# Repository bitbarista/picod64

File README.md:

# PicoD64: a cycle-exact 1541 emulator you can build

<div align="center">

-0369a1)

</div>

PicoD64 replaces a Commodore 1541 disk drive, using a Raspberry Pi Pico 2. It doesn't imitate
the drive's behaviour from the outside: it **emulates the 1541's electronics**. The drive's 6502,
its two 6522 VIAs and the GCR data path to the head are emulated cycle by cycle, in lockstep at
1 MHz, and they run the 1541's own DOS ROM, which you supply. Disk images come from a microSD
card, and it plugs into the C64's serial (IEC) port like a drive. Because the DOS and any drive
code a program uploads run cycle for cycle, fast loaders behave as they do on a 1541: demanding demo loaders
run on a real C64 (see [Compatibility](#compatibility)).

It is designed to be cheap and easy to build: a small board, almost all through-hole (the
microSD socket and the Pico 2's castellated edge are surface-soldered), a Pico 2, a 1.3" OLED,
a rotary encoder and a 3D-printed case.

> **Free for private and commercial use.** PicoD64 is a hobby project, given to the community.
> Build one, sell them, improve them; if you change it, share your changes under the same terms
> (see [Licence](#licence)). If it's useful to you, please consider
> [supporting it on Ko-fi](https://ko-fi.com/bitbarista). It funds the prototypes and test hardware.
>
> **Ordering boards?** Signing up to JLCPCB through [this referral link](https://jlcpcb.com/?from=PBTJYEXOJNFQR) costs you nothing
> extra and earns the project a small credit towards new prototypes.

<div align="center">
  
</div>

## Download

Click a link and the file downloads; there's no need to find your way round GitHub.

| | |
|---|---|
| **Firmware** | [**picod64.uf2**](https://github.com/bitbarista/picod64/releases/latest/download/picod64.uf2): copy it onto the Pico (see [Firmware and SD card](#firmware-and-sd-card)). |
| **The 1541 ROM for the SD card** | The [**card setup page**](https://bitbarista.github.io/picod64/fw/tools/card-setup.html) fetches it, checks it and saves it for the card. |
| **The board** | [**picod64-rev1.1-gerbers.zip**](https://github.com/bitbarista/picod64/releases/latest/download/picod64-rev1.1-gerbers.zip): send this file to a PCB maker as it is. |
| **The case** | [**picod64-case-stl.zip**](https://github.com/bitbarista/picod64/releases/latest/download/picod64-case-stl.zip): every part to print, as STL files. |
| **Using it** | The [**user guide**](docs/USER-GUIDE.md): the browser, the knob and OLED, and multi-disk games, with pictures. |
| **Building it** | The [**interactive BOM**](https://bitbarista.github.io/picod64/hardware/fab/picod64-ibom.html) shows where each part goes; [`hardware/BUILD-NOTES.md`](hardware/BUILD-NOTES.md) is the step-by-step guide. |
| **Everything** | [**The whole project as one zip**](https://github.com/bitbarista/picod64/archive/refs/heads/main.zip): the source, the parts lists and all the documents. |

Older versions and the notes for each are on the [Releases page](https://github.com/bitbarista/picod64/releases).

## Highlights

| | |
|---|---|
| **Change disks with one hold of the knob.** For multi-disk games and demos: hold the knob and PicoD64 swaps to the next disk of the set, as you'd swap floppies, and the C64 carries on. The OLED shows which disk is in (`2/3`). | **A knob and display on the drive.** Insert, swap and eject disks, make a new blank one, or set the device number, without touching the C64. Everything the browser does is shown there too. See the [user guide](docs/USER-GUIDE.md). |
| **The 1541's electronics, emulated.** The drive's 6502, VIAs and GCR path are emulated cycle by cycle, running the 1541's own DOS ROM. Fast loaders and drive code should behave as they do on a 1541. | **Cheap and easy to build.** A Raspberry Pi Pico 2 and common parts, almost all through-hole, with ready-made Farnell and LCSC order files. No programmer: flash it by copying one file over USB. |
| **An all-new browser, built in.** Nothing to install on the card or the C64: `LOAD"*",8`, `RUN`. Full upper/lower-case names, a format column, multi-disk sets told apart, type to filter, keyboard or joystick. | **Turbo loading, ~27× faster.** About 11 KB/s with no drive code, and it falls back to a plain load on any error. One key turns it off for awkward or copy-protected titles. |
| **A case designed for it.** A 3D-printed case made to fit this board, with C64-style ribs, shoulders and printed badges, including a PWR/ACT badge like the breadbin's POWER badge. Prints without supports or a brim, and every part is fit-checked against it. | **Writes for real.** SAVE, scratch and format go back into the D64 on the card. With no disk mounted, `SAVE` writes a PRG and `N:` makes a new blank disk. |
| **Sounds like a 1541.** A piezo plays the head stepping, the head bump knock and the motor, driven by what the emulated drive is doing. | **Fits in with what you have.** A second IEC socket daisy-chains on to other drives, device 8–11. Made for FB64 and FB64 Turbo, and for JiffyDOS with your own ROM (both pass the PC tests; not yet confirmed on a real C64). |

**Open.** Hardware CERN-OHL-W, code GPL-3.0. Written clean-room from datasheets and Commodore's own documents, with every source listed.

**Proven on a real C64:** the drive and its DOS, the browser and its turbo, and a list of demanding demo loaders and the 1541 Testsuite (see [Compatibility](#compatibility)). JiffyDOS (KERNAL, and KERNAL plus drive ROM) is proven on a real C64 too. FB64 and the turbo's speed figure come from the PC tests so far: [Status](#status-rev-11-november-2026) says what is proven where.

## What it does

In detail.

- **The 1541, emulated cycle for cycle.** Every cycle of the drive's 6502 and VIAs is emulated, in
  lockstep with the IEC bus, running the stock DOS ROM (325302-01 + 901229-05) that you supply on the card.
  SAVE, scratch and format work, and what you write goes back into the D64 on the card. With no disk
  mounted, `SAVE` writes a PRG to the card, and `N:NAME,ID` makes a new blank D64. The knob's **Settings** has **New disk** too.
- **D64 images from microSD**, up to 42 tracks. FAT32 or exFAT, any size, folders anywhere. A mounted image is
  streamed to GCR a track at a time. Written tracks go back to the file when the motor stops,
  before a disk swap or an eject, and when the card-detect switch sees the card being pulled
  (eject first to be safe).
- **Browse mode.** With no disk mounted, the C64 sees the card itself: `LOAD"$",8` lists the
  folder, `.PRG` files load directly, and you `CD` into a folder or a D64 to mount it.
- **A built-in browser for the C64.** `LOAD"*",8` then `RUN`, or `LOAD"BROWSER",8` the plain way. Full
  names in upper and lower case, with a column showing each file's format, so `game.d64`, `game.prg` and
  `game.crt` can be told apart, and a footer that says what RETURN will do. Keyboard or joystick in port 2:
  cursor keys and RETURN, type to filter, DEL for back, F1 for options (Run, Load, Run slow; for a disk Open,
  Run first, Insert), RUN/STOP to quit. Folders of any size; up to 2,048 entries are listed, and the filter
  reaches the rest. It remembers the turbo setting, the folder and the position on the card.
- **A turbo for the browser.** Programs (PRG files) on the card load at about 11 KB/s, ~27× stock (on
  the PC twin), with no drive code. Programs inside a D64 load the normal 1541 way, through the drive, so the
  drive has read the disk as a real one would. F3 turns it off, F1 Run slow skips it once, and any wrong byte falls
  back to a plain LOAD.
- **FB64 file browsers.** Made to work with Jani's **FB64** (FB v2.0), its fast-loader version
  **FB v2.0FL**, and **FB64 Turbo** ([CSDb 223021](https://csdb.dk/release/?id=223021)): browsing,
  mounting and loading, including FB64 Turbo's turbo loads from a D64 or a PRG. All three pass on
  the PC against the real KERNAL; the first board will try them on a real C64.
- **Display and knob.** A 1.3" OLED shows the folder and the mounted disk. The knob scrolls, pushes
  to mount and ejects. **Settings** is the last line of the list, one click back from the top. A **long press mounts the next disk of a set** (`disk1`, `side a`,
  `1a`, `(Disk 1 of 3)` and similar names), for multi-disk games and demos. A green PWR and a red ACT
  LED, the 1541's colours, stand proud of the lid.
  **Try it before you build:** [open the front panel demo](https://bitbarista.github.io/picod64/host/panel-demo/panel-demo.html)
  in your browser. It runs the real knob and OLED code, in a picture of the case. To keep a copy that works offline,
  download [`panel-demo.html`](host/panel-demo/panel-demo.html) and open it.
- **Daisy chain.** Two IEC sockets wired in parallel: one to the C64, one on to the next device.
  The device number can be set to 8–11: hold the knob at power-on, turn, press. It is shown on the OLED.
- **It sounds like a 1541.** A small piezo plays the head stepping, the knock of a head
  bump and the motor, driven by what the emulated drive is really doing. *Sound* in the knob's **Settings** turns it off.
- **Powered by USB.** An optional header takes 5 V from the C64's datasette port instead, but
  that port is rated for only about 100 mA, so whether it is enough is still to be measured.

## The built-in browser

There's nothing to install or copy to the card, and nothing to add to the C64. It's in the firmware: `LOAD"*",8`, then `RUN`.

- **Fast.** Programs load at about 11 KB/s, roughly 27 times stock, with no drive code. It's measured on the PC test setup so far, not yet on a real C64.
- **You can see what you're choosing.** Full names in upper and lower case. A format column tells `game.d64` from `game.prg` and `game.crt`, and a footer says what RETURN will do.
- **Which disk is which.** A column reads the disk and side from the name, so a long name's `(Disk 1 of 2 Side A)` shows as `1A` even when the row has to shorten it.
- **Made for real collections.** A folder of 802 long names opens in about 0.75 s on the test setup, with up to 2,048 entries listed in order. Type a few letters to filter, including entries past that limit.
- **Keyboard or joystick.** Cursor keys and RETURN, DEL for back, F1 for options (Run, Load, Run slow; on a disk Open, Run first, Insert), F3 for the turbo. It's all on screen, so there's nothing to memorise.
- **Remembers where you were.** The folder, your position and the turbo setting are kept on the card.
- **Fits in with what you have.** It's designed to start with a fast-load cartridge fitted, runs with a JiffyDOS KERNAL on the test setup, and works on a plain 1541 too. FB64 and others still work if you prefer them: none of this needs the browser.

## Status (rev 1.1, November 2026)

- **The first board is built and works with a real C64.** Rev 1.1 is the same board with the new name on the
  silkscreen; copper and drill files are identical ([`hardware/AUDIT.md`](hardware/AUDIT.md) R25).
- **The emulator is proven on the PC.** The 6502 passes Klaus Dormann's functional test and is
  bus-identical, cycle by cycle, to perfect6502. The stock DOS boots exactly as in VICE. The
  real C64 KERNAL lists and loads from it over a simulated IEC bus, byte-identical to VICE.
  Writes are read back correctly by VICE's `c1541`.
- **The board firmware is built and host-tested.** The drive runs in real time on a Pico 2
  (lockstep at 150 MHz). The whole board code (SD, FatFs, browse mode, mount, write-back,
  fast-loader handling, knob, OLED) is tested on the PC against the real KERNAL and a simulated
  SD card ([`host/fwtwin.sh`](host/fwtwin.sh), over 100 checks).
- **On a real C64, at the stock 150 MHz:** the DOS, the browser and its fast loader, and demanding demo loaders
  (The Hat, Edge of Disgrace, MATH, each through every disk), checked against a real-timing drive on the same C64
  with a bus sniffer. [`FIRMWARE.md`](FIRMWARE.md) has the measurements and the known issues.
- **The case is printed:** the split lid, C64-style details, badges and knob are confirmed by print. A fit check of
  every part on the assembled board against the case passes ([`case/check_fit.py`](case/check_fit.py)).

**Still to measure:** power from the datasette port; more fast loaders and games.

**Known limits.** D64 images of 35, 40 and 42 tracks. A D64's error bytes are built into the disk, so the DOS
finds each read error where the original disk had it; the write errors they can record are not. No G64, no D71/D81. The 6502's undocumented opcodes pass the 1541 Testsuite; its IRQ/SO edge
timing is not yet checked against perfect6502.

## Compatibility

Tested on a real **PAL** C64 with the stock 150 MHz firmware, PicoD64 the only device on the serial bus, each
title from a freshly powered-up C64 and run to its end (or its own pass screen):

- **Demos and their loaders:** Coma Light 13 (Krill's loader), Dutch Breeze, Edge of Disgrace and Uncensored
  (Booze Design), Lunatico and Shards of Fancy (Spindle), MATH, Memento Mori (Sparkle), Primitive 7 Sins,
  Reanim8ed (Dasheles' loader), The Hat, The Masque, Transwarp (the fastest loader about), Wonderland XIV (40
  tracks), Mafio-DOS.
- **The drive's CPU:** the 1541 Testsuite (r192), all 219 tests.
- **The browser and its turbo,** loading PRGs (turbo) and D64s (the normal 1541 way) from the card.

That is a sample, not every program. PicoD64 is checked against a real 1541 wherever we could, but **we can't
be sure everything runs**: some loaders are famously picky, and there are thousands of titles.
[`docs/COMPAT-TESTS.md`](docs/COMPAT-TESTS.md) has the list, with each title's loader and disks. Some fast loaders fail with another drive
or interface on the serial bus, on a real 1541 too: if one fails, try PicoD64 as the only device.

**PAL only so far.** Every test was on a PAL C64. PicoD64 is designed for NTSC too (the drive runs on its own 1 MHz
clock, as a 1541 does, and the browser's turbo allows for both C64 clocks), but it has **not been tested on an NTSC
C64**. Reports from NTSC owners are welcome (the bug report link below).

**If something doesn't work, please [open an issue](https://github.com/bitbarista/picod64/issues/new?template=bug_report.md).**
Say what you ran (title, group, and a CSDb link or where the image came from), how you started it (the browser,
`LOAD"*",8,1`, a cartridge), what happened and when, and which firmware ([`firmware/VERSION.txt`](firmware/VERSION.txt)). If you have a
real 1541 or another drive to hand, whether it works there helps a lot.

## How it works

- **Two cores.** Core 1 owns the IEC pins and nothing else. It runs either browse mode or the
  emulated 1541, from SRAM, in lockstep with the bus. Core 0 owns the SD card, the OLED, the
  knob, the LEDs and the piezo. When browse mode needs the card, core 1 holds the bus busy, as a
  real drive does, while core 0 does the work.
- **The ATN acknowledge in PIO.** A real 1541 answers ATN with an XOR gate, in nanoseconds. Some
  fast loaders, FB64 Turbo among them, check for the answer 4 µs later, too soon for software,
  so a PIO state machine ([`fw/atn_gate.pio`](fw/atn_gate.pio), 5 instructions) answers instead. Measured on the
  bus of a real C64: DATA follows an ATN edge 0.17 µs later when pulled, 0.42 µs when released (the
  line's slower rise); a 1541 on the same C64, 0.25 µs.
- **Fast loaders from browse mode.** When a C64 program uploads drive code in browse mode,
  PicoD64 builds a disk on the card, boots the emulated 1541 with its DOS, replays the conversation
  into it, then hands the bus to the emulated drive.
- **White-coat design.** PicoD64's own code is written from primary documentation: datasheets,
  Commodore's documents and the ROM itself. Other implementations, VICE among them, are used
  only as black-box oracles to compare results against. [`PROVENANCE.md`](PROVENANCE.md) lists every source and
  the few exceptions (FB64 Turbo's source was read, for compatibility only). Third-party code,
  FatFs, keeps its own licence ([`THIRD-PARTY.md`](THIRD-PARTY.md)).

## Building one

1. **Order the board** from JLCPCB ([referral link](https://jlcpcb.com/?from=PBTJYEXOJNFQR)) or
   any fab: [`picod64-rev1.1-gerbers.zip`](https://github.com/bitbarista/picod64/releases/latest/download/picod64-rev1.1-gerbers.zip) (also in [`hardware/fab/`](hardware/fab/)), 2 layers, 1.6 mm.
2. **Buy the parts:** [`hardware/fab/BUY.md`](hardware/fab/BUY.md), with a ready-made Farnell upload file in [`hardware/fab/`](hardware/fab/). Farnell
   is the tested source; an LCSC file is there too, but it has never been ordered. The full BOM, with the optional parts, is [`hardware/fab/BOM.md`](hardware/fab/BOM.md).
3. **Solder it.** Almost everything is through-hole. The interactive BOM
   ([open it](https://bitbarista.github.io/picod64/hardware/fab/picod64-ibom.html), or download
   [`hardware/fab/picod64-ibom.html`](hardware/fab/picod64-ibom.html) and open it in a browser)
   shows where each part goes and lets you tick parts off as you fit them. The Pico 2 is soldered flat by its
   castellated edge, and the microSD socket is surface-mount, with every tail reachable by an iron.
   **[`hardware/BUILD-NOTES.md`](hardware/BUILD-NOTES.md) is the step-by-step build:** fit order, polarities, LED standoffs, the OLED,
   the first test, printing and assembling the case.
4. **Print the case:** every file in [`picod64-case-stl.zip`](https://github.com/bitbarista/picod64/releases/latest/download/picod64-case-stl.zip) (the same as [`case/stl/`](case/stl/)), as exported, with **no brim** and no supports
   ([`hardware/BUILD-NOTES.md`](hardware/BUILD-NOTES.md), step 6). The badges print best in two colours: change filament
   at the letters. The set includes a small **knob seating tool**: push the knob onto it once before fitting it, so its
   first, firm push is on the bench and not on the encoder ([`hardware/BUILD-NOTES.md`](hardware/BUILD-NOTES.md), step 7).
5. **Flash the firmware and prepare the card** (below).

### Firmware and SD card

- **Flash:** hold the Pico's BOOTSEL (in the case: press the pinhole marked ⤓ with a paperclip),
  plug in USB, and copy [**picod64.uf2**](https://github.com/bitbarista/picod64/releases/latest/download/picod64.uf2) (click to download; it's also [`firmware/picod64.uf2`](firmware/picod64.uf2)) onto
  the **RP2350** drive that appears.
- **Updating, once flashed:** copy the new `picod64.uf2` to the card's top folder and switch on. PicoD64
  checks it, installs it (the OLED says *Updating, wait*, then *Updated*) and renames it
  `picod64.uf2.done`. Don't switch off while it updates; if that ever happens, flash it with BOOTSEL as above.
- **SD card:** any size, formatted FAT32 or exFAT. Put your disk images (`.d64`) and programs
  (`.prg`) on it, in folders if you like.
- **The 1541 DOS ROM.** PicoD64's emulated 1541 runs the drive's own operating system, so it needs a
  copy of the drive's ROM. The ROM is Commodore's copyright, so PicoD64 can't include it; you put it on the
  card yourself. The ROMs are archived at [zimmers.net](https://www.zimmers.net/anonftp/pub/cbm/firmware/).
  - **The easy way, any computer:** open the **[card setup page](https://bitbarista.github.io/picod64/fw/tools/card-setup.html)**
    and click *Get the 1541 ROM*. It fetches the ROM from zimmers.net, joins and checks it, and saves `dos1541.bin`
    for the card (in Chrome or Edge, straight onto the card). It takes your own copy instead if you have one, and
    can add the Commodore font for the OLED too. Nothing to install, and the page holds no ROMs. It also works
    downloaded: save [`card-setup.html`](fw/tools/card-setup.html) and open it in a browser.
  - **Windows, with a script:** download [`get-roms.ps1`](fw/tools/get-roms.ps1), open **PowerShell**
    in the folder you saved it to, and run (with your card's drive letter):

        powershell -ExecutionPolicy Bypass -File get-roms.ps1 E:\

    It downloads the ROMs, joins and checks them, and writes them to the card.
    (`-ExecutionPolicy Bypass` lets this one script run; Windows blocks downloaded scripts by default.)
  - **Windows, by hand:** download the two halves of the 1541 ROM,
    [`1541-c000.325302-01.bin`](https://www.zimmers.net/anonftp/pub/cbm/firmware/drives/new/1541/1541-c000.325302-01.bin)
    and [`1541-e000.901229-05.bin`](https://www.zimmers.net/anonftp/pub/cbm/firmware/drives/new/1541/1541-e000.901229-05.bin),
    open **Command Prompt** (not PowerShell: there `copy` works differently) in the folder they are in, and join them:

        copy /b 1541-c000.325302-01.bin + 1541-e000.901229-05.bin dos1541.bin

    Copy `dos1541.bin` to the top folder of the card.
  - **Linux or macOS:** `bash fw/tools/get-roms.sh /path/to/the/card` does the same as the Windows
    script. By hand: `cat 1541-c000.325302-01.bin 1541-e000.901229-05.bin > dos1541.bin`.
  - It must be exactly **16,384 bytes**, MD5 `a0ce8439d1b8dcf2e1430461f7233a72`: that is the ROM
    PicoD64 is tested with (on Windows, `certutil -hashfile dos1541.bin MD5` shows it). If the file is
    missing or the wrong size, the OLED shows *Need /dos1541.bin*.
- **Optional: a different font on the OLED.** It comes with a C64-style font, and you can change it by
  adding one file to the top folder of the card:
  - **A plainer font, same size:** copy [`fw/fonts/font5x7.bin`](fw/fonts/font5x7.bin) to the card.
  - **The Commodore font itself:** this one is wider, so names get 14 characters instead of 19. The card setup
    page adds it (step 2), or put the C64's character ROM,
    [`characters.901225-01.bin`](https://www.zimmers.net/anonftp/pub/cbm/firmware/computers/c64/characters.901225-01.bin),
    on the card renamed **`chargen.bin`**. The scripts don't add it. If both files are there, this one wins.
- **Optional, for JiffyDOS owners:** if your C64 has the JiffyDOS KERNAL and you own the JiffyDOS
  1541 ROM, put that ROM (16,384 bytes) on the card as `dos1541.bin` instead. Mounted D64s then
  load at JiffyDOS speed: on a real C64, a 154-block file took 18-20 s instead of about 100 s, every
  byte checked ([Compatibility](#compatibility)). Not included, because JiffyDOS is a commercial product.

### Building from source

- **Firmware:** `bash fw/build.sh` builds `fw/build/picod64.uf2` (the release's [`firmware/picod64.uf2`](firmware/picod64.uf2) is that file). It needs the Raspberry Pi Pico
  SDK and the Arm GNU toolchain.
- **Host checks:** `sh host/check.sh` runs every emulator and firmware check on the PC. It needs
  Klaus Dormann's functional test, perfect6502 and the C64/1541 ROMs, which are not included;
  the scripts say where they look.
- **Hardware:** the KiCad 9 project is in [`hardware/`](hardware/), generated by [`hardware/gen/`](hardware/gen/): the
  schematic by `gen/check_sch.sh`, the board by `gen/board.sh` (with Freerouting), the order
  files by `gen/fab.py`, and the interactive BOM by `gen/ibom.py` (it needs InteractiveHtmlBom; the
  script says how to install it). The makers' 3D models of the sockets and encoder can't be
  redistributed, so they are not included: `bash hardware/lib/3d/fetch.sh` gets them.
- **Case:** [`case/picod64-case.scad`](case/picod64-case.scad) (OpenSCAD). Use **Window > Customizer** for the fit,
  screws, walls, labels and knob, then run `bash case/export.sh` to re-export and re-check every
  part. The scripts read the values written in the scad, not Customizer presets.
  - **Font:** the labels use **Eurostile**, a commercial font that is not included. Without it,
    OpenSCAD silently uses another font and the letter spacing goes wrong. To use a font you
    have, run `bash case/gen_glyphs.sh "Your Font"`, set `LABEL_FONT` at the top of the scad,
    then run `bash case/check_labels.sh`. Wide, squared fonts suit the case; free examples are
    Michroma and Orbitron.

## Documents

| File | What |
|---|---|
| [`docs/USER-GUIDE.md`](docs/USER-GUIDE.md) | Using it: the browser, the knob and OLED, multi-disk games |
| [`hardware/BUILD-NOTES.md`](hardware/BUILD-NOTES.md) | Building it: soldering, OLED, printing the case, screws, firmware and SD card |
| [`FIRMWARE.md`](FIRMWARE.md) | The firmware: test gates, results, the board firmware's design and status |
| [`hardware/AUDIT.md`](hardware/AUDIT.md) | The design audit: every decision and check, with its evidence |
| [`case/CASE.md`](case/CASE.md) | The case: printing, customising, and its design history |
| [`PROVENANCE.md`](PROVENANCE.md) | Sources for every factual claim in the design |
| [`THIRD-PARTY.md`](THIRD-PARTY.md) | Third-party material: what is included, what isn't, and why |

| Folder | What |
|---|---|
| [`core/`](core/) | The emulator: `cpu6502.h`, `via6522.h`, `drive1541.h`, browse mode. Shared by the PC checks and the Pico |
| [`fw/`](fw/) | The board firmware |
| [`host/`](host/) | PC checks: Klaus test, perfect6502 bus comparison, DOS boot, IEC, the firmware twin |
| [`bench/`](bench/) | The feasibility firmware for a bare Pico 2 |
| [`hardware/`](hardware/) | KiCad project, generators, fab files |
| [`case/`](case/) | The 3D-printed case: OpenSCAD source, STLs, checks, renders |

## Not in this release

This repository is the release: everything needed to build PicoD64, change it and test it. The development
history stays in the project's own repository: superseded case designs and test prints (`archive/`, which
`case/CASE.md` and `hardware/AUDIT.md` mention), a styling study, the rev 1 fab files as ordered (rev 1.1 has the
same copper), and the early feasibility notes and hardware proposal.

## Support the project

PicoD64 took a lot of design and test work, and prototype boards cost money. If you build one,
a coffee on Ko-fi is very welcome:

New to JLCPCB? Signing up through [this referral link](https://jlcpcb.com/?from=PBTJYEXOJNFQR) also helps: it earns the project
a small credit towards new prototypes, at no cost to you.

## Disclaimer

PicoD64 is a hobby project, provided as is, without warranty of any kind. Building it and using
it are at your own risk. The author accepts no responsibility for damage to your C64, your
drives or other hardware, for lost or corrupted disk images or data, or for any other loss.

- **Switch the C64 and other drives off** before connecting or disconnecting the serial (IEC)
  cable.
- **Keep copies of your disk images.** PicoD64 writes to the D64 files on the card. A firmware
  fault, a card pulled while writing or a power cut can damage them.
- **ROMs and software are yours to supply.** PicoD64 includes no Commodore ROMs and no games.

The full terms are in the licences below.

## Licence

© 2026 Carl Leach. Free for private and commercial use. **Modifications must be shared under the
same terms**: if you distribute a changed design, firmware or document, its source goes with it
under the same licence.

- **Hardware and case design** ([`hardware/`](hardware/), [`case/`](case/)): [CERN-OHL-W v2](LICENSES/CERN-OHL-W-2.0.txt)
- **Emulator, firmware, tools and checks** ([`core/`](core/), [`fw/`](fw/), [`host/`](host/), [`bench/`](bench/), [`hardware/gen/`](hardware/gen/),
  and the scripts): [GPL-3.0-only](LICENSES/GPL-3.0.txt)
- **Documentation:** [CC BY-SA 4.0](LICENSES/CC-BY-SA-4.0.txt)

Third-party code keeps its own licence: FatFs by ChaN ([`fw/fatfs/`](fw/fatfs/)), the Bescii font (CC0,
[`fw/fonts/bescii/`](fw/fonts/bescii/)), footprints adapted from the KiCad libraries (CC BY-SA 4.0) and the Raspberry
Pi Pico SDK (BSD-3-Clause, fetched at build time). [LICENSE.md](LICENSE.md) says which licence
covers which folder; [THIRD-PARTY.md](THIRD-PARTY.md) has the details.

*Not affiliated with, or endorsed by, any holder of the Commodore trademarks, or Raspberry Pi Ltd.*

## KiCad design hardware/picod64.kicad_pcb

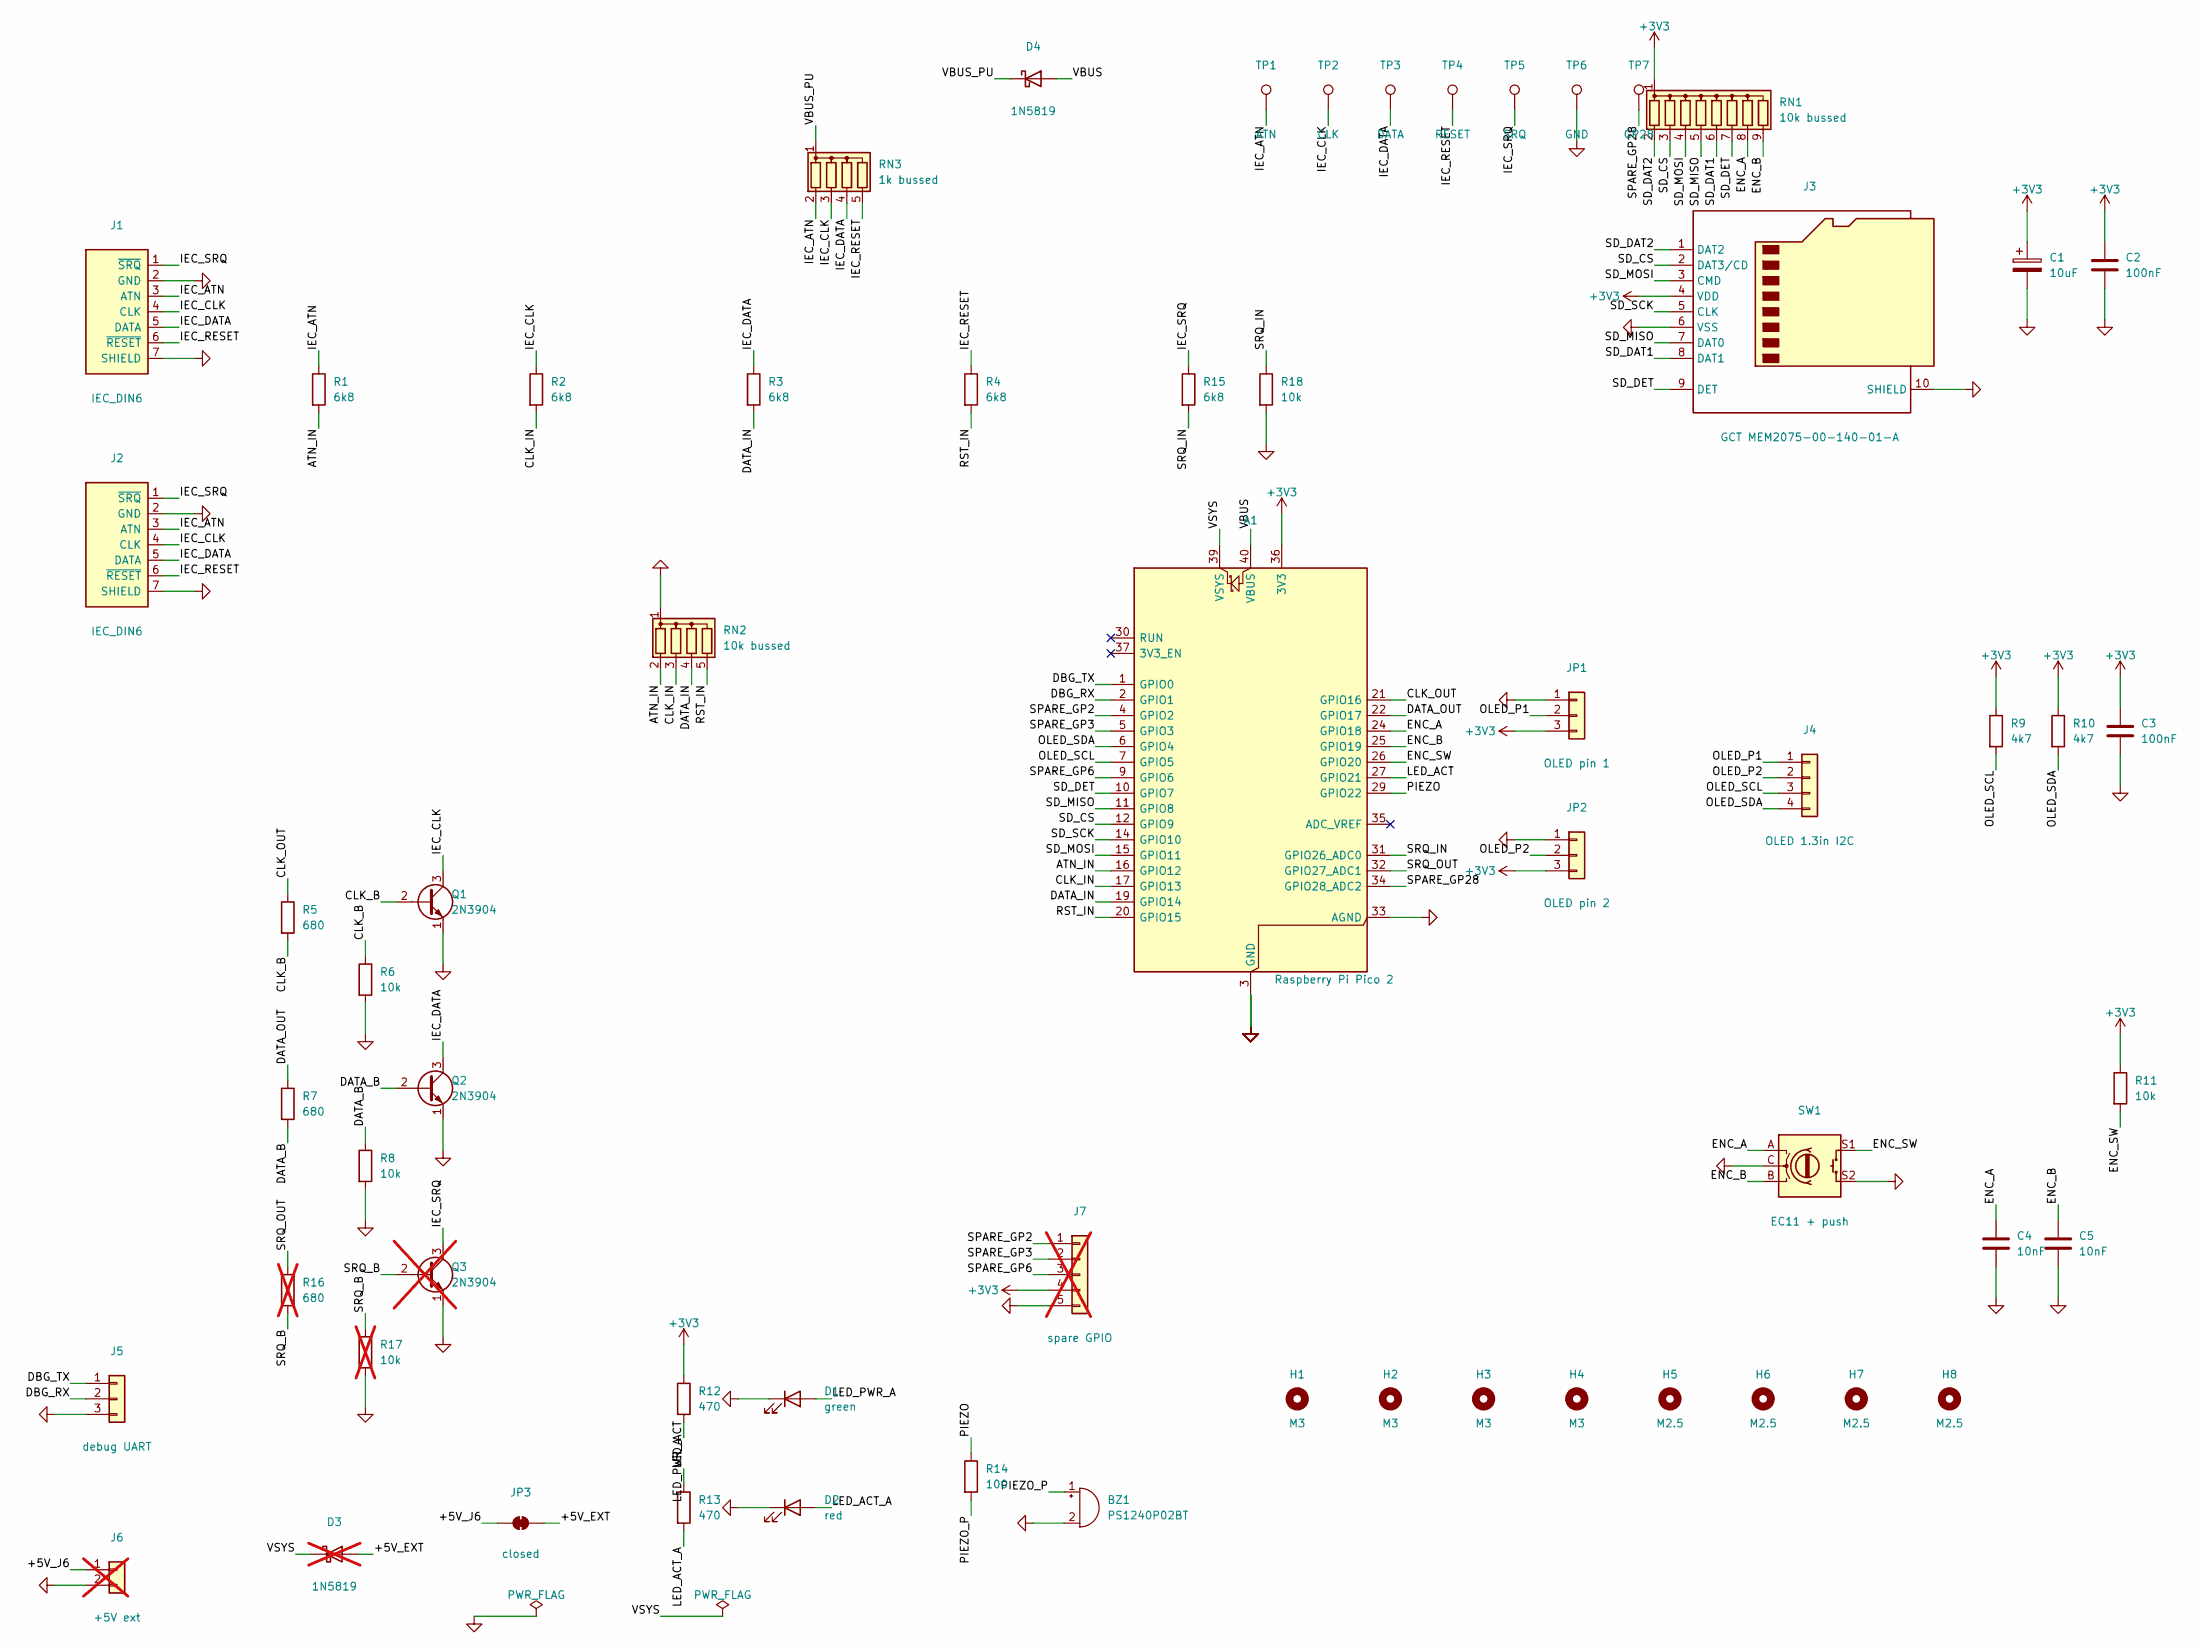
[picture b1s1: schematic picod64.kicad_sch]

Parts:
A1: Raspberry Pi Pico 2; RaspberryPi_Pico_SMD_HandSolder_Pin1Rect
BZ1: PS1240P02BT; Buzzer_TDK_PS1240P02BT_D12.2mm_H6.5mm
C1: 10uF; CP_Radial_D5.0mm_P2.00mm
C2, C3: 100nF; C_Disc_D3.0mm_W2.0mm_P2.50mm
C4, C5: 10nF; C_Disc_D3.0mm_W2.0mm_P2.50mm
D1: green; LED_D3.0mm
D2: red; LED_D3.0mm
D3: 1N5819; D_DO-41_SOD81_P10.16mm_Horizontal; not fitted
D4: 1N5819; D_DO-41_SOD81_P10.16mm_Horizontal
H1, H2, H3, H4: M3; MountingHole_3.2mm_M3
H5, H6, H7, H8: M2.5; MountingHole_2.7mm_M2.5
J1, J2: IEC_DIN6; IEC_DIN6_DualEarth
J3: GCT MEM2075-00-140-01-A; microSD_GCT_MEM2075
J4: OLED 1.3in I2C; PinSocket_1x04_P2.54mm_Vertical
J5: debug UART; PinHeader_1x03_P2.54mm_Vertical
J6: +5V ext; PinHeader_1x02_P2.54mm_Vertical; not fitted
J7: spare GPIO; PinHeader_1x05_P2.54mm_Vertical; not fitted
JP1: OLED pin 1; PinHeader_1x03_P2.54mm_Vertical
JP2: OLED pin 2; PinHeader_1x03_P2.54mm_Vertical
JP3: closed; SolderJumper-2_P1.3mm_Bridged_RoundedPad1.0x1.5mm
Q1, Q2: 2N3904; TO-92_Inline_Wide
Q3: 2N3904; TO-92_Inline_Wide; not fitted
R1, R2, R3, R4, R15: 6k8; R_Axial_DIN0207_L6.3mm_D2.5mm_P7.62mm_Horizontal
R5, R7: 680; R_Axial_DIN0207_L6.3mm_D2.5mm_P7.62mm_Horizontal
R6, R8, R11: 10k; R_Axial_DIN0207_L6.3mm_D2.5mm_P7.62mm_Horizontal
R9, R10: 4k7; R_Axial_DIN0207_L6.3mm_D2.5mm_P7.62mm_Horizontal
R12, R13: 470; R_Axial_DIN0207_L6.3mm_D2.5mm_P7.62mm_Horizontal
R14: 100; R_Axial_DIN0207_L6.3mm_D2.5mm_P7.62mm_Horizontal
R16: 680; R_Axial_DIN0207_L6.3mm_D2.5mm_P7.62mm_Horizontal; not fitted
R17: 10k; R_Axial_DIN0207_L6.3mm_D2.5mm_P7.62mm_Horizontal; not fitted
R18: 10k; R_Axial_DIN0207_L6.3mm_D2.5mm_P2.54mm_Vertical
RN1: 10k bussed; R_Array_SIP9
RN2: 10k bussed; R_Array_SIP5
RN3: 1k bussed; R_Array_SIP5
SW1: EC11 + push; EC11E_Switch_Alps
TP1: ATN; TestPoint_THTPad_D2.0mm_Drill1.0mm
TP2: CLK; TestPoint_THTPad_D2.0mm_Drill1.0mm
TP3: DATA; TestPoint_THTPad_D2.0mm_Drill1.0mm
TP4: RESET; TestPoint_THTPad_D2.0mm_Drill1.0mm
TP5: SRQ; TestPoint_THTPad_D2.0mm_Drill1.0mm
TP6: GND; TestPoint_THTPad_D2.0mm_Drill1.0mm
TP7: GP28; TestPoint_THTPad_D2.0mm_Drill1.0mm

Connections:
+3V3: A1.36 (3V3), C1.1, C2.1, C3.1, J3.4 (VDD), J7.4, JP1.3, JP2.3, R9.1, R10.1, R11.1, R12.1, RN1.1 (common)
/+5V_EXT: D3.2 (A), JP3.2 (B)
/+5V_J6: J6.1, JP3.1 (A)
/ATN_IN: A1.16 (GPIO12), R1.2, RN2.2 (R1)
/CLK_B: Q1.2 (B), R5.2, R6.1
/CLK_IN: A1.17 (GPIO13), R2.2, RN2.3 (R2)
/CLK_OUT: A1.21 (GPIO16), R5.1
/DATA_B: Q2.2 (B), R7.2, R8.1
/DATA_IN: A1.19 (GPIO14), R3.2, RN2.4 (R3)
/DATA_OUT: A1.22 (GPIO17), R7.1
/DBG_RX: A1.2 (GPIO1), J5.2
/DBG_TX: A1.1 (GPIO0), J5.1
/ENC_A: A1.24 (GPIO18), C4.1, RN1.8 (R7), SW1.A
/ENC_B: A1.25 (GPIO19), C5.1, RN1.9 (R8), SW1.B
/ENC_SW: A1.26 (GPIO20), R11.2, SW1.S1
/IEC_ATN: J1.3 (ATN), J2.3 (ATN), R1.1, RN3.2 (R1), TP1.1
/IEC_CLK: J1.4 (CLK), J2.4 (CLK), Q1.3 (C), R2.1, RN3.3 (R2), TP2.1
/IEC_DATA: J1.5 (DATA), J2.5 (DATA), Q2.3 (C), R3.1, RN3.4 (R3), TP3.1
/IEC_RESET: J1.6 (~RESET), J2.6 (~RESET), R4.1, RN3.5 (R4), TP4.1
/IEC_SRQ: J1.1 (~SRQ), J2.1 (~SRQ), Q3.3 (C), R15.1, TP5.1
/LED_ACT: A1.27 (GPIO21), R13.1
/LED_ACT_A: D2.2 (A), R13.2
/LED_PWR_A: D1.2 (A), R12.2
/OLED_P1: J4.1, JP1.2
/OLED_P2: J4.2, JP2.2
/OLED_SCL: A1.7 (GPIO5), J4.3, R9.2
/OLED_SDA: A1.6 (GPIO4), J4.4, R10.2
/PIEZO: A1.29 (GPIO22), R14.1
/PIEZO_P: BZ1.1 (+), R14.2
/RST_IN: A1.20 (GPIO15), R4.2, RN2.5 (R4)
/SD_CS: A1.12 (GPIO9), J3.2 (DAT3/CD), RN1.3 (R2)
/SD_DAT1: J3.8 (DAT1), RN1.6 (R5)
/SD_DAT2: J3.1 (DAT2), RN1.2 (R1)
/SD_DET: A1.10 (GPIO7), J3.9 (DET), RN1.7 (R6)
/SD_MISO: A1.11 (GPIO8), J3.7 (DAT0), RN1.5 (R4)
/SD_MOSI: A1.15 (GPIO11), J3.3 (CMD), RN1.4 (R3)
/SD_SCK: A1.14 (GPIO10), J3.5 (CLK)
/SPARE_GP2: A1.4 (GPIO2), J7.1
/SPARE_GP3: A1.5 (GPIO3), J7.2
/SPARE_GP6: A1.9 (GPIO6), J7.3
/SPARE_GP28: A1.34 (GPIO28_ADC2), TP7.1
/SRQ_B: Q3.2 (B), R16.2, R17.1
/SRQ_IN: A1.31 (GPIO26_ADC0), R15.2, R18.1
/SRQ_OUT: A1.32 (GPIO27_ADC1), R16.1
/VBUS: A1.40 (VBUS), D4.2 (A)
/VBUS_PU: D4.1 (K), RN3.1 (common)
/VSYS: A1.39 (VSYS), D3.1 (K)
GND: A1.3 (GND), A1.8 (GND), A1.13 (GND), A1.18 (GND), A1.23 (GND), A1.28 (GND), A1.33 (AGND), A1.38 (GND), BZ1.2 (-), C1.2, C2.2, C3.2, C4.2, C5.2, D1.1 (K), D2.1 (K), J1.2 (GND), J1.7 (SHIELD), J2.2 (GND), J2.7 (SHIELD), J3.6 (VSS), J3.10 (SHIELD), J5.3, J6.2, J7.5, JP1.1, JP2.1, Q1.1 (E), Q2.1 (E), Q3.1 (E), R6.2, R8.2, R17.2, R18.2, RN2.1 (common), SW1.C, SW1.S2, TP6.1

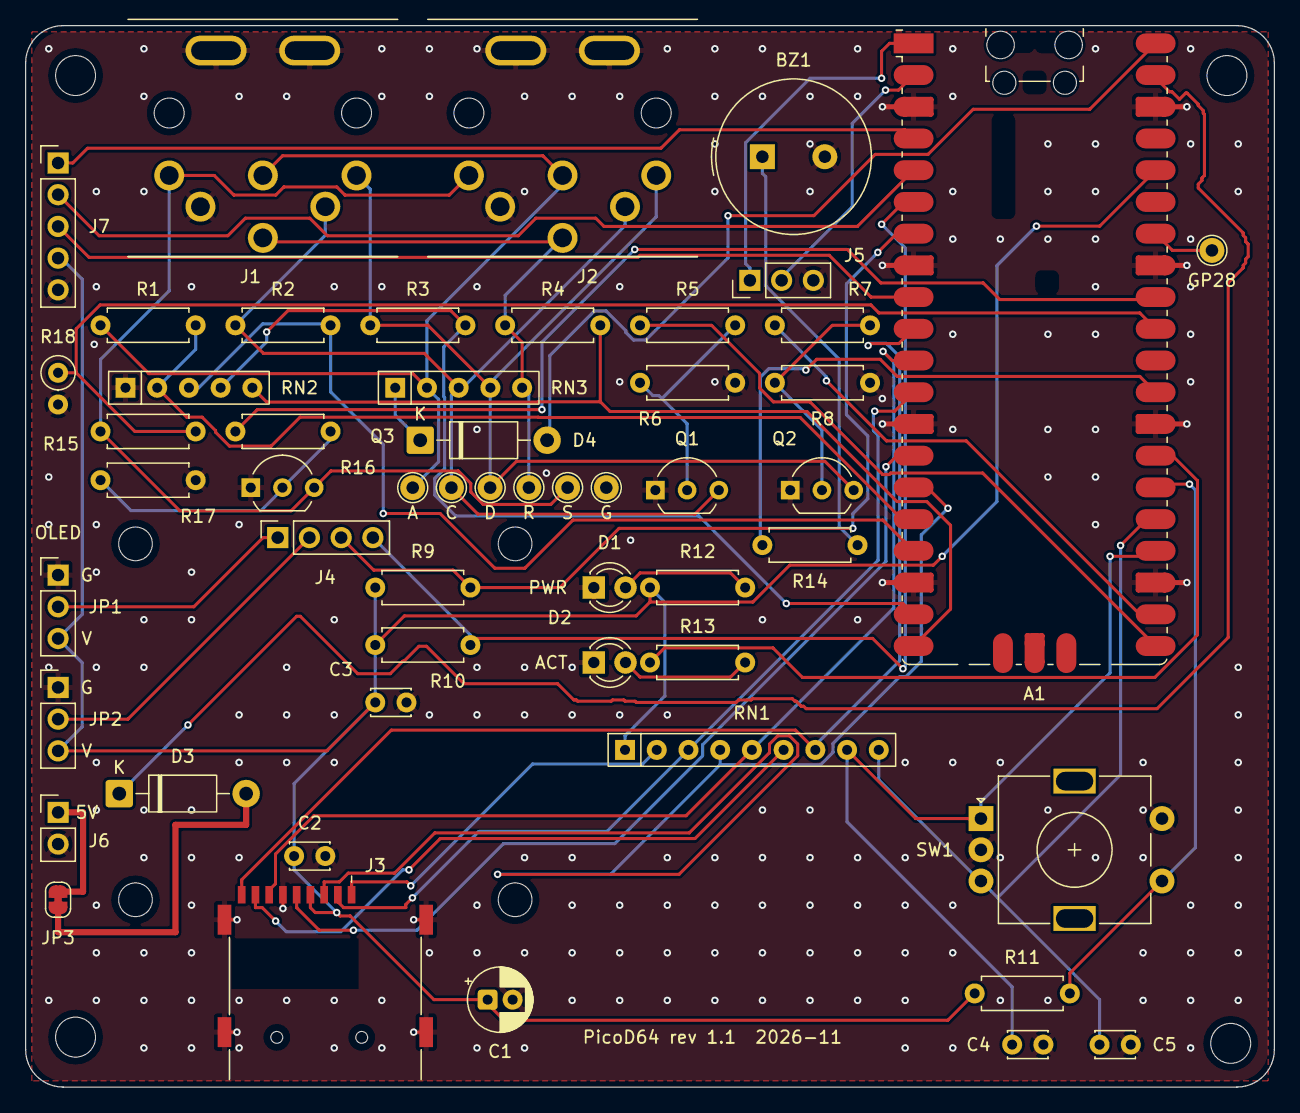
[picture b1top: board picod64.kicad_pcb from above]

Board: 2 copper layers, 100.0 x 85.0 mm, 61 parts (0 on the bottom side), 48 nets.

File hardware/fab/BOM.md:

# PicoD64 rev 1.1: bill of materials

Generated by [`hardware/gen/fab.py`](../gen/fab.py) from the schematic. Farnell UK stock checked 2026-10-26 (hardware/AUDIT.md F1). [C] = choose by the spec given.

## On the board (fit)

| Refs | Qty | Value | Part | Maker / MPN | Farnell UK | Notes |
|---|---|---|---|---|---|---|
| A1 | 1 | Raspberry Pi Pico 2 | Raspberry Pi Pico 2 (RP2350), no headers; soldered flat on its castellations | Raspberry Pi SC1631 | 4531086 |  |
| BZ1 | 1 | PS1240P02BT | Piezo transducer, external drive, Ø12.2 x 6.5 mm, 5.0 mm pitch | TDK PS1240P02BT | 3267212 | drive sounds, always fitted (AUDIT R40); 12,019 in stock 2026-10-26. NOT a magnetic/self-drive buzzer |
| C1 | 1 | 10uF | Electrolytic 10 µF 50 V, 5 x 11 mm, 2.0 mm pitch | Multicomp Pro MCGPR50V106M5X11 | 9451382 | + to the square pad |
| C2 C3 | 2 | 100nF | Ceramic 100 nF 50 V X7R, radial, 2.5 mm lead spacing | Vishay K104K15X7RF53L2 | 1141775 | suffix L2 = straight 2.5 mm [D: Vishay 45171]; 165,160 in stock 2026-10-26. NOT ...TH5 (5.0 mm) |
| C4 C5 | 2 | 10nF | Ceramic 10 nF 50 V X7R, radial, 2.5 mm lead spacing | Vishay K103K15X7RF53L2 | 1141772 | L2 = straight 2.5 mm; 35,115 in stock 2026-10-26. NOT ...TH5 (5.0 mm) |
| D1 | 1 | green | LED 3 mm green diffused, 568 nm, 8-20 mcd @ 10 mA | Kingbright L-934GD | 1142502 | same family as D2 (L-934); flat/short leg = square pad |
| D2 | 1 | red | LED 3 mm high-efficiency red diffused, 625 nm, 8-20 mcd @ 10 mA | Kingbright L-934ID | 1142517 | same family as D1; R13 470R -> ~2.8 mA from GP21 (< 4 mA drive) |
| D4 | 1 | 1N5819 | Schottky 1N5819, DO-41 | Vishay 1N5819-E3/54 | 1336533 | blocks the bus powering the Pico; band (K) toward RN3 pin 1 |
| J1 J2 | 2 | IEC_DIN6 | DIN 6-pin 240° socket, right angle, PCB | Lumberg 0105 06 | 2677786 | Same Sky SDF-60J also fits the footprint |
| J3 | 1 | GCT MEM2075-00-140-01-A | microSD socket, push-push, all tails exposed | GCT MEM2075-00-140-01-A | 2895610 | LCSC C3029735; the only SMD part (drag-solder, flux) |
| J4 | 1 | OLED 1.3in I2C | Socket 1 x 4, 2.54 mm, 8.5 mm high | Würth 61300411821 | 2827888 | the OLED plugs in here, last |
| J5 | 1 | debug UART | Pin header 1 x 3, 2.54 mm (debug UART) | Würth 61304011121 (cut) |  | 3 pins cut from the 1 x 40 strip |
| JP1 JP2 | 2 | OLED pin 1/OLED pin 2 | Pin header 1 x 3, 2.54 mm | Würth 61304011121 (cut) |  | 3 pins cut from the 1 x 40 strip; each takes a jumper cap |
| Q1 Q2 | 2 | 2N3904 | NPN 2N3904, TO-92 (E-B-C) | onsemi 2N3904BU | 1700648 | bend the outer legs out to the 2.54 mm holes; flat face as the silk |
| R1 R2 R3 R4 R15 | 5 | 6k8 | Resistor 6k8 1 % 0.25 W metal film | Multicomp Pro MF25 6K8 | 9342168 |  |
| R12 | 1 | 470 | Resistor 470R 1 % 0.25 W | Multicomp Pro MF25 470R | 9341943 | was 1k: 470R matches D1 to D2 (~2.8 mA each) |
| R13 | 1 | 470 | Resistor 470R 1 % 0.25 W | Multicomp Pro MF25 470R | 9341943 |  |
| R14 | 1 | 100 | Resistor 100R 1 % 0.25 W | Multicomp Pro MF25 100R | 9341099 | BZ1 series |
| R5 R7 | 2 | 680 | Resistor 680R 1 % 0.25 W | Multicomp Pro MF25 680R | 9342150 |  |
| R6 R8 R11 R18 | 4 | 10k | Resistor 10k 1 % 0.25 W | Multicomp Pro MF25 10K | 9341110 | R18 stands upright (2.54 mm holes), at the left edge |
| R9 R10 | 2 | 4k7 | Resistor 4k7 1 % 0.25 W (I²C pull-ups) | Multicomp Pro MF25 4K7 | 9341951 | always fitted: fine with or without pull-ups on the module (AUDIT R37); under the module, so fit before it |
| RN1 | 1 | 10k bussed | Resistor network 10k x 8, bussed, SIP-9 (pin 1 = common, dot) | Bourns 4609X-101-103LF | 9356819 | pin 1 = square pad |
| RN2 | 1 | 10k bussed | Resistor network 10k x 4, bussed, SIP-5 (pin 1 = common, dot) | Bourns 4605X-101-103LF | 9356061 | pin 1 = square pad |
| RN3 | 1 | 1k bussed | Resistor network 1k x 4, bussed, SIP-5 | Bourns 4605X-101-102LF | 9356053 | 1k bus pull-ups, as a real 1541; pin 1 (dot) = square pad; only on USB power (AUDIT R39) |
| SW1 | 1 | EC11 + push | Rotary encoder with push switch, 15 PPR / 30 detents, 20 mm D shaft, 0.5 mm travel | Alps Alpine EC11E15244G1 | 2064986 | NOT the B2 (1.5 mm travel): the knob would bottom |

## Optional (do not fit for a standard build)

| Refs | Qty | Value | Part | Maker / MPN | Farnell UK | Notes |
|---|---|---|---|---|---|---|
| D3 | 1 | 1N5819 | Schottky 1N5819, DO-41 | Vishay 1N5819-E3/54 | 1336533 | only with J6 (external 5 V) |
| J6 | 1 | +5V ext | Pin header 1 x 2, 2.54 mm | Würth 61304011121 (cut) |  | external 5 V, with D3; 2 pins cut from the strip |
| J7 | 1 | spare GPIO | Pin header 1 x 5, 2.54 mm (spare GP2/3/6, 3V3, GND) | Würth 61304011121 (cut) |  | optional; 5 pins cut from the 1 x 40 strip |
| Q3 | 1 | 2N3904 | NPN 2N3904, TO-92 (E-B-C) | onsemi 2N3904BU | 1700648 | SRQ out (rev 1): fit only if a fast serial mode ever needs it, with R16 and R17 |
| R16 | 1 | 680 | Resistor 680R 1 % 0.25 W | Multicomp Pro MF25 680R | 9342150 | with Q3 only |
| R17 | 1 | 10k | Resistor 10k 1 % 0.25 W | Multicomp Pro MF25 10K | 9341110 | with Q3 only |

## Not on the board

| Qty | Part | Maker / MPN | Farnell UK | Notes |
|---|---|---|---|---|
| 1 | Pin header strip 1 x 40, 2.54 mm, breakaway: cut J5, JP1, JP2 (3 each), J6 (2), J7 (5) | Würth 61304011121 | 2356175 | one strip instead of three Harwin lines (Farnell minimums of 10-100) |
| 2 | Jumper cap 2.54 mm (JP1, JP2) | Harwin M7686-46 | 3756818 | order code unique in Farnell search (M7566-05's 150411 was not) |
| 4 | Printed OLED pillar, snaps into H5-H8 (case file, part "oled_pillars") |  |  | no screws: they slide onto the module's edges (BUILD-NOTES: OLED) |
| 1 | OLED module 1.3" SH1106, I²C, 4-pin (VCC/GND order either way) | [C] any |  | measure it for the pillars (BUILD-NOTES: OLED) |
| 4 | M2.6 x 16 countersunk self-tapping screw | [C] any |  | from below into the lid posts (picod64-lid-front.stl + picod64-lid-rear.stl) |
| (4) | OPTIONAL: M3 x 16 countersunk machine screw + M3 heat-set insert (Ø4.0 mm hole, <= 7 mm long) | [C] any |  | instead, only with the picod64-lid-*-insert.stl pair, for a case opened often |
| 4 | Self-adhesive rubber foot, 10 mm (max 10.6) | [C] any |  | stick on over the screw heads, centred in the rings marked round them |
| 2 | Printed LED standoff (case file, part "led_standoffs") |  |  | sets D1/D2 so the dome stands 1.5 mm proud of the lid; needs >= 14 mm of LED lead |
| 1 | Printed case: tray; lid front + lid rear, top face down; knob; 4 OLED pillars; 2 LED standoffs; 3 badges; the knob seating tool (no brim, no supports) |  |  | case/picod64-case.scad |

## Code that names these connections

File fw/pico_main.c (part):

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#define PIN_TX 0
#define PIN_SDA 4
#define PIN_SCL 5
#define PIN_SD_DET 7
#define PIN_SD_MISO 8
#define PIN_SD_CS 9
#define PIN_SD_SCK 10
#define PIN_SD_MOSI 11
#define PIN_ATN_IN 12            /* 12-15: ATN CLK DATA RESET, pin high = line released (divider) */
#define PIN_RST_IN 15
#define PIN_CLK_OUT 16           /* 16-17: CLK DATA, pin high = line pulled LOW (2N3904) */
#define PIN_DATA_OUT 17
#define PIN_ENC_A 18
#define PIN_ENC_B 19
/* B, A into enc_update: with A, B the knob ran backwards on the first board (2026-11-06); the
 * direction in ui.c was an assumption [A], this is the real board's */
#define PIN_ENC_SW 20
#define PIN_LED 21
#define PIN_PIEZO 22

#define DEMCR      (*(volatile uint32_t *)0xE000EDFCu)
#define DWT_CTRL   (*(volatile uint32_t *)0xE0001000u)
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static uint8_t tr_gate[LOG_N];
#endif
static uint8_t log_last = 0xFF;
static inline uint8_t pins_in(void) { return (uint8_t)((~sio_hw->gpio_in >> PIN_ATN_IN) & 7); }
/* CLK_OUT (GP16) from the SIO; DATA_OUT (GP17) from the ATN gate's PIO state machine:
 * gate config bit 0 = pull DATA while ATN released, bit 1 = while asserted */
#define GATE_PIO pio0
#define GATE_SM  0
static inline void gate_set(uint32_t cfg) { pio_sm_put(GATE_PIO, GATE_SM, cfg); }
static inline void clk_set(int pull) { if (pull) sio_hw->gpio_set = 1u << PIN_CLK_OUT; else sio_hw->gpio_clr = 1u << PIN_CLK_OUT; }
static inline void pins_out(uint8_t pulls)        /* browse mode: IECD_CLK (2), IECD_DATA (4), whatever ATN does */
{
    clk_set(pulls & 2);
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static uint32_t bus_us(void) { return time_us_32(); }
static uint8_t bus_in(void) { return pins_in(); }
static void bus_out(uint8_t p) { pins_out(p); }
static int bus_reset(void) { return !((sio_hw->gpio_in >> PIN_RST_IN) & 1); }
/* a RESET pulse since the last look: GPIO15's falling edge, latched in the raw interrupt status whether or not the
 * interrupt is enabled; reading clears it (fw/bus.h BUS_RESET_EDGE) */
static inline int bus_reset_edge(void)
{
    uint32_t m = GPIO_IRQ_EDGE_FALL << (4 * (PIN_RST_IN % 8));
    if (!(io_bank0_hw->intr[PIN_RST_IN / 8] & m)) return 0;
    io_bank0_hw->intr[PIN_RST_IN / 8] = m;           /* write 1 to clear */
    return 1;
}
#define BUS_RESET_EDGE() bus_reset_edge()
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#include "ui.h"
#include "update.h"
uint8_t sd_spi_xfer(uint8_t out) { uint8_t in; spi_write_read_blocking(spi1, &out, &in, 1); return in; }
void sd_spi_cs(int low) { gpio_put(PIN_SD_CS, !low); }
void sd_spi_speed(int f) { spi_set_baudrate(spi1, f ? 25000000 : 400000); }
uint32_t sd_ms(void) { return to_ms_since_boot(get_absolute_time()); }
int sd_present(void) { return !gpio_get(PIN_SD_DET); }   /* [A] the switch closes to GND with a card in */

static unsigned card_tries, card_removals;   /* (serial 's': the card going and coming, 2026-11-09) */
static long rq_read_n, rq_read_last; static char rq_read_path[44];   /* (serial 's': the last card read, 2026-11-07) */
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{
    int dev = bus_device, redraw = 1;
    ui_draw_device(ui, dev); oled_show(ui);           /* at once: the knob is still down, show it worked */
    while (!gpio_get(PIN_ENC_SW)) sleep_ms(10);       /* the press that got us here is not the save */
    sleep_ms(50);
    for (;;) {
        uint32_t ms = sd_ms();
        int ev = enc_update(knob, gpio_get(PIN_ENC_B), gpio_get(PIN_ENC_A), gpio_get(PIN_ENC_SW), ms);
        if (ev == EV_PRESS) break;
        int next = ui_device_step(dev, ev);
        if (next != dev) { dev = next; redraw = 1; }
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static volatile uint16_t snd_test;                   /* serial T: samples of a full-swing 3.9 kHz test tone */
static void snd_irq(void)
{
    pwm_clear_irq(pwm_gpio_to_slice_num(PIN_PIEZO));
    if ((snd_odd ^= 1)) return;
    if (snd_test) { snd_test--; pwm_set_gpio_level(PIN_PIEZO, (snd_test & 2) ? SND_WRAP + 1u : 0); return; }
    int online = *(volatile int *)&B.online;
    uint8_t d = snd_tick(&snd, *(volatile uint8_t *)&D.phase, *(volatile uint8_t *)&D.ht, online && (via_pb(&D.via2) & 0x04), online,
                         B.dev.listening || B.dev.talking, snd_on);
    pwm_set_gpio_level(PIN_PIEZO, (uint16_t)((d * (SND_WRAP + 1u)) >> 8));
}
static void snd_start(void)
{
    snd_on = (uint8_t)svc_sound_get();
    uint slice = pwm_gpio_to_slice_num(PIN_PIEZO);
    pwm_set_wrap(slice, SND_WRAP);
    pwm_set_gpio_level(PIN_PIEZO, 0);
    gpio_set_function(PIN_PIEZO, GPIO_FUNC_PWM);
    gpio_set_drive_strength(PIN_PIEZO, GPIO_DRIVE_STRENGTH_12MA); gpio_set_slew_rate(PIN_PIEZO, GPIO_SLEW_RATE_FAST);   /* R14 sets the edge current */
    pwm_clear_irq(slice); pwm_set_irq_enabled(slice, true);
    irq_set_exclusive_handler(PWM_IRQ_WRAP_0, snd_irq);
    irq_set_enabled(PWM_IRQ_WRAP_0, true);
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{
    /* lines (serial a, 2026-11-18): the answer is a change of CLK or DATA on the bus, not on our outputs, so the same rule
     * times any drive: PicoD64, or with it off the bus (X) another drive on the cable */
    const uint32_t ATN = 1u << PIN_ATN_IN, OUTS = lines ? 6u << PIN_ATN_IN : 3u << PIN_CLK_OUT, US = SYS_MHZ, RD = 4060u * SYS_MHZ / 1000u;
    DEMCR |= 1u << 24; DWT_CTRL |= 1;
    uint32_t hist[16] = {0}, n = 0, skipped = 0, worst_n = 0; int32_t mmin = INT32_MAX;
    struct { int32_t m, ans; uint32_t ms; uint16_t pc; uint8_t ht, rise, kind; } w[8];
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    /* G3 (2026-11-21, hardware/IEC-TIMING-DECISION.md): which edge each answer was. kind: bit 0 CLK changed, 1 CLK went
     * high, 2 DATA changed, 3 DATA went high (on the bus lines: high = released; from our outputs: high = pulled). Late
     * answers (margin < 0) and near ones (< 0.5 us) are counted per line and direction */
    const uint32_t C_B = lines ? 1u << (PIN_ATN_IN + 1) : 1u << PIN_CLK_OUT, D_B = lines ? 1u << (PIN_ATN_IN + 2) : 1u << PIN_DATA_OUT;
    uint8_t ans_kind = 0; uint32_t late_k[4] = {0}, near_k[4] = {0};   /* [line*2 + released]: 0 CLK pull 1 CLK release 2 DATA pull 3 DATA release */
    printf("answer watch (%s): a key stops it\n", lines ? "from the bus lines" : "from our outputs");
    for (;;) {
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#define EW_HELD 0xFFFFu
static int __not_in_flash_func(edge_slice)(uint32_t *vp, uint16_t *rec, int max, uint32_t dur)
{
    const uint32_t MASK = (3u << PIN_CLK_OUT) | (3u << (PIN_ATN_IN + 1)), US = SYS_MHZ;
    uint32_t v = *vp, t_start = DWT_CYCCNT, t0[2] = {0, 0}; int pend[2] = {-1, -1}, n = 0;   /* pend: the change waited for */
    while (n < max) {
        uint32_t nv, t;
        do { nv = sio_hw->gpio_in & MASK; t = DWT_CYCCNT; } while (nv == v && t - t_start < dur);
        if (nv == v) break;
        for (int l = 0; l < 2; l++) {
            const uint32_t O = 1u << (PIN_CLK_OUT + l), I = 1u << (PIN_ATN_IN + 1 + l);
            if ((nv ^ v) & O) {                              /* our output changed: pull (pin high) or release */
                int k = (nv & O) ? 0 : 1;
                pend[l] = ((nv & I) != 0) == (k == 0) ? k : -1;   /* the line not already where it's going */
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static uint16_t pt_t[4][8]; static uint8_t pt_v[4][8], pt_n[4];
static void __not_in_flash_func(pulse_run)(uint16_t r[][3], int n, uint32_t *iters, int l)
{
    const uint32_t O = 1u << (PIN_CLK_OUT + l), I = 1u << (PIN_ATN_IN + 1 + l), TO = 10u * SYS_MHZ, GAP = 20u * SYS_MHZ;
    uint32_t t0 = DWT_CYCCNT, k = 0;
    while (DWT_CYCCNT - t0 < SYS_MHZ) { (void)sio_hw->gpio_in; k++; }   /* 1 us of the polling's own loop */
    *iters = k;
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    DEMCR |= 1u << 24; DWT_CTRL |= 1;
    for (int l = 0; l < 2; l++) {
        const char *nm = l ? "DATA" : "CLK";
        if (!(sio_hw->gpio_in & (1u << (PIN_ATN_IN + 1 + l))) || (sio_hw->gpio_in & (1u << (PIN_CLK_OUT + l)))) { printf("pulse test %s: not idle (held low, or ours pulled)\n", nm); continue; }
        uint32_t irq = save_and_disable_interrupts();
        pulse_run(r, 100, &it, l);
        restore_interrupts(irq);
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static inline void lt_out(int l, int pull)
{
    if (l) gate_set(pull ? 1u : 0u);                 /* (the gate's "pull while ATN released": ATN stays released) */
    else if (pull) sio_hw->gpio_set = 1u << PIN_CLK_OUT; else sio_hw->gpio_clr = 1u << PIN_CLK_OUT;
}
static int __not_in_flash_func(lt_trial_pins)(int l, int pull, uint32_t d)
{
    const uint32_t TRIG = 1u << (PIN_ATN_IN + (l ? 1 : 2)), US = SYS_MHZ;
    uint32_t t0 = DWT_CYCCNT, te;
    while (!(sio_hw->gpio_in & TRIG)) if (DWT_CYCCNT - t0 > 5000u * US) return -1;   /* released first */
    while (sio_hw->gpio_in & TRIG) if (DWT_CYCCNT - t0 > 5000u * US) return -1;      /* the C64's pull */
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    if (B.online) { printf("line timing: eject first\n"); return; }
    int was_off = bus_off; bus_off = 1; sleep_ms(2);   /* core 1 lets go and parks */
    DEMCR |= 1u << 24; DWT_CTRL |= 1;
    const uint32_t BOTH = 3u << (PIN_ATN_IN + 1);
    int there = 0;
    printf("line timing: waiting up to 60 s for LINETIME on the C64 (a key stops it)\n");
    for (int t = 0; t < 600 && !there; t++) {        /* hello: CLK and DATA pulled 10 ms, then a trial within 90 ms */
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    for (int l = 0; l < 2; l++) for (int k = 0; k < 2; k++) { s[l][k].n = s[l][k].sum = s[l][k].max = 0; s[l][k].min = UINT32_MAX; for (int i = 0; i < 16; i++) s[l][k].hist[i] = 0; }
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

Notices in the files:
README.md:
License: hardware
License: code
